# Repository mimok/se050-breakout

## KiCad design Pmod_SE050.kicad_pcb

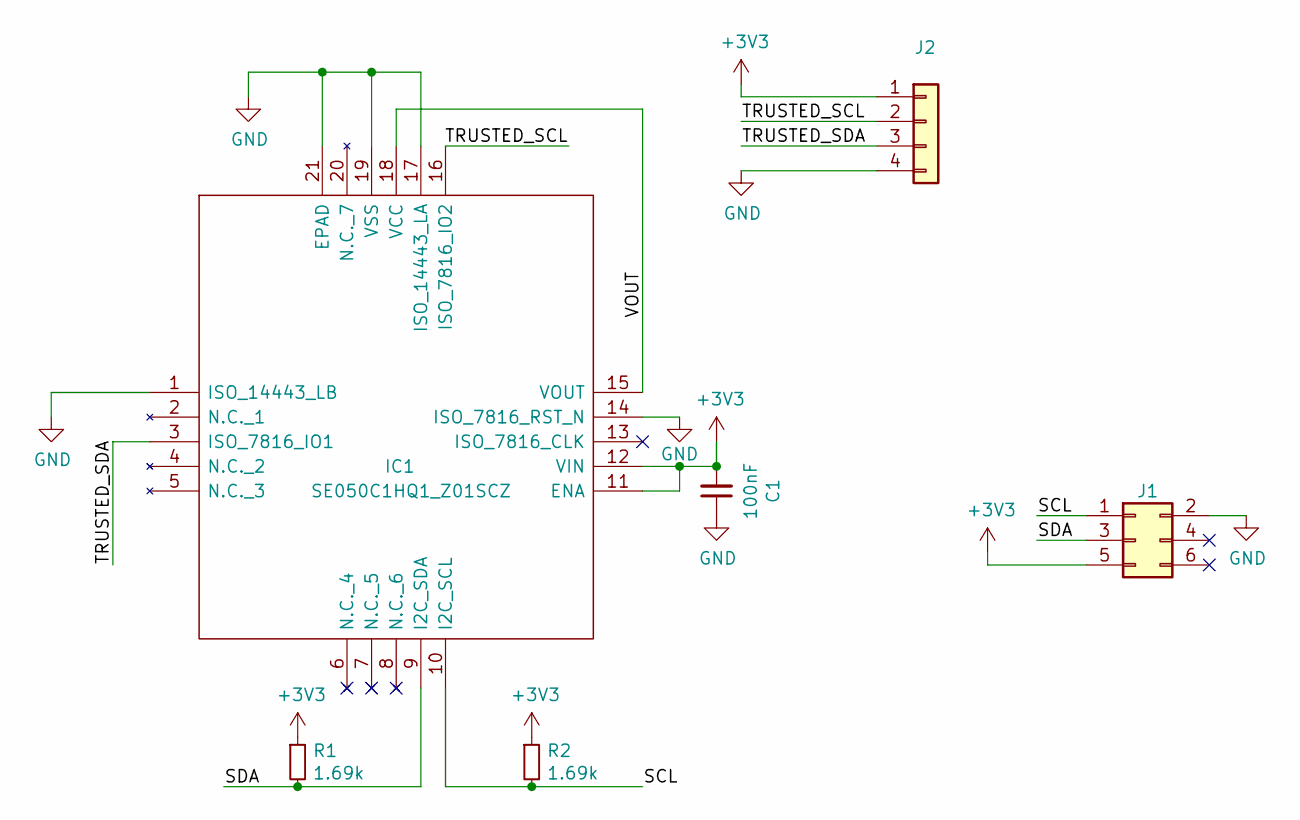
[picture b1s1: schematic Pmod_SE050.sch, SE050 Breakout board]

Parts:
C1: 100nF; C_0603
IC1: SE050C1HQ1_Z01SCZ; QFN40P300X300X33-21N-D; Manufacturer_Part_Number SE050C1HQ1/Z01SCZ
J1: Conn_02x03_Odd_Even; PinHeader_2x03_P2.54mm_Vertical
J2: Conn_01x04; PinHeader_1x04_P2.54mm_Vertical
R1, R2: 1.69k; R_0603

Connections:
+3V3: C1.2, IC1.11 (ENA), IC1.12 (VIN), J1.5, J2.1, R1.1, R2.1
/SCL: IC1.10 (I2C_SCL), J1.1, R2.2
/SDA: IC1.9 (I2C_SDA), J1.3, R1.2
/TRUSTED_SCL: IC1.16 (ISO_7816_IO2), J2.2
/TRUSTED_SDA: IC1.3 (ISO_7816_IO1), J2.3
/VOUT: IC1.15 (VOUT), IC1.18 (VCC)
GND: C1.1, IC1.1 (ISO_14443_LB), IC1.14 (ISO_7816_RST_N), IC1.17 (ISO_14443_LA), IC1.19 (VSS), IC1.21 (EPAD), J1.2, J2.4

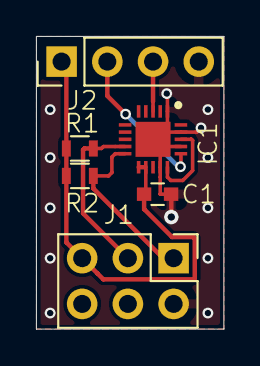
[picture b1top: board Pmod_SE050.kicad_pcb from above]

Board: 2 copper layers, 10.4 x 16.3 mm, 6 parts (0 on the bottom side), 7 nets.

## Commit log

2020-11-28 Update LICENSE
    Full license instead of summarize
2022-01-08 Rev 2.0 of the board
    New version of the breakout board.
    Schematic is the same but the board is smaller.

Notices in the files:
Pmod_SE050.kicad_pcb:
Creative Commons CA-BY 4.0
